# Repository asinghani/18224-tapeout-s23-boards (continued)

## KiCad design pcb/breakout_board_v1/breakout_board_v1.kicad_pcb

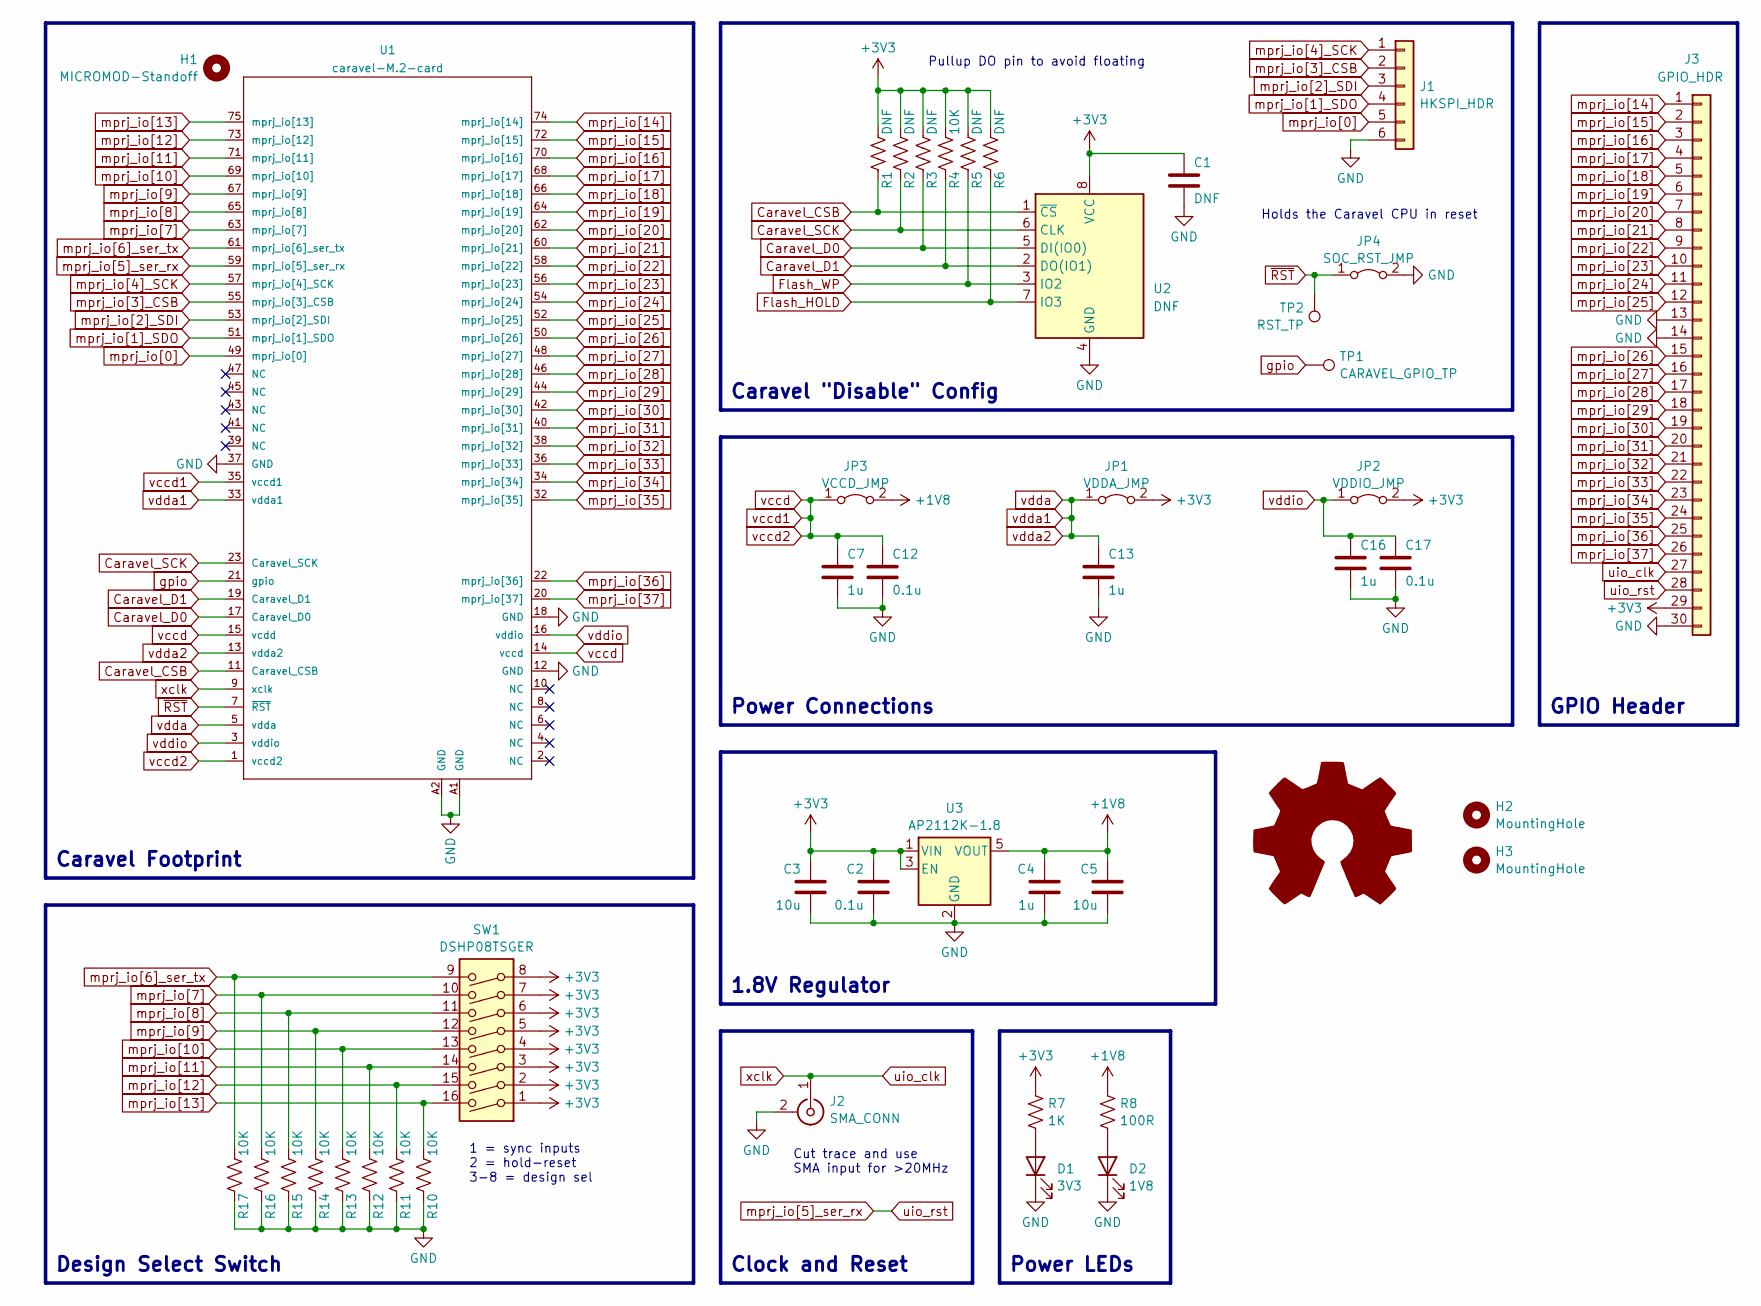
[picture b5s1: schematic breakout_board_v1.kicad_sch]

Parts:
C1: DNF; C_0603_1608Metric_Pad1.08x0.95mm_HandSolder
C2, C12, C17: 0.1u; C_0603_1608Metric; LCSC C14663
C3, C5: 10u; C_0603_1608Metric; LCSC C19702
C4, C7, C13, C16: 1u; C_0603_1608Metric; LCSC C15849
D1: 3V3; LED_0805_2012Metric; LCSC C98221
D2: 1V8; LED_0805_2012Metric; LCSC C98221
H1: MICROMOD-Standoff; MicroMod-Standoff
H2, H3: MountingHole; MountingHole_3.2mm_M3_Pad_Via
J1: HKSPI_HDR; PinHeader_1x06_P2.54mm_Vertical
J2: SMA_CONN; SMB_Jack_Vertical
J3: GPIO_HDR; PinHeader_1x30_P2.54mm_Vertical
JP1: VDDA_JMP; SolderJumper-2_P1.3mm_Bridged2Bar_Pad1.0x1.5mm
JP2: VDDIO_JMP; SolderJumper-2_P1.3mm_Bridged2Bar_Pad1.0x1.5mm
JP3: VCCD_JMP; SolderJumper-2_P1.3mm_Bridged2Bar_Pad1.0x1.5mm
JP4: SOC_RST_JMP; SolderJumper-2_P1.3mm_Bridged2Bar_Pad1.0x1.5mm
R1, R2, R3, R5, R6: DNF; R_0805_2012Metric
R4, R10, R11, R12, R13, R14, R15, R16, R17: 10K; R_0805_2012Metric; LCSC C17414
R7: 1K; R_0805_2012Metric; LCSC C17513
R8: 100R; R_0805_2012Metric; LCSC C17408
SW1: DSHP08TSGER; SW_DIP_SPSTx08_Slide_KingTek_DSHP08TS_W7.62mm_P1.27mm; LCSC C3293147
TP1: CARAVEL_GPIO_TP; TestPoint_Pad_D1.5mm
TP2: RST_TP; TestPoint_Pad_D1.5mm
U1: caravel-M.2-card; M.2-CONNECTOR-E; LCSC C2977809
U2: DNF; SOIC-8_5.23x5.23mm_P1.27mm
U3: AP2112K-1.8; SOT-23-5; LCSC C176944

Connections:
+1V8: C4.1, C5.1, JP3.2 (B), R8.2, U3.5 (VOUT)
+3V3: C1.1, C2.1, C3.1, J3.29, JP1.2 (B), JP2.2 (B), R1.1, R2.1, R3.1, R4.1, R5.1, R6.1, R7.2, SW1.1, SW1.2, SW1.3, SW1.4, SW1.5, SW1.6, SW1.7, SW1.8, U2.8 (VCC), U3.1 (VIN), U3.3 (EN)
Caravel_CSB: R1.2, U1.11 (Caravel_CSB), U2.1 (~CS)
Caravel_D0: R3.2, U1.17 (Caravel_D0), U2.5 (DI(IO0))
Caravel_D1: R4.2, U1.19 (Caravel_D1), U2.2 (DO(IO1))
Caravel_SCK: R2.2, U1.23 (Caravel_SCK), U2.6 (CLK)
Flash_HOLD: R6.2, U2.7 (IO3)
Flash_WP: R5.2, U2.3 (IO2)
GND: C1.2, C2.2, C3.2, C4.2, C5.2, C7.2, C12.2, C13.2, C16.2, C17.2, D1.1 (K), D2.1 (K), J1.6, J2.2 (Ext), J3.13, J3.14, J3.30, JP4.2 (B), R10.2, R11.2, R12.2, R13.2, R14.2, R15.2, R16.2, R17.2, U1.12 (GND), U1.18 (GND), U1.37 (GND), U1.A1 (GND), U1.A2 (GND), U2.4 (GND), U3.2 (GND)
unnamed: D1.2 (A), R7.1
unnamed: D2.2 (A), R8.1
gpio: TP1.1, U1.21 (gpio)
mprj_io[0]: J1.5, U1.49 (mprj_io[0])
mprj_io[1]_SDO: J1.4, U1.51 (mprj_io[1]_SDO)
mprj_io[2]_SDI: J1.3, U1.53 (mprj_io[2]_SDI)
mprj_io[3]_CSB: J1.2, U1.55 (mprj_io[3]_CSB)
mprj_io[4]_SCK: J1.1, U1.57 (mprj_io[4]_SCK)
mprj_io[5]_ser_rx: J3.28, U1.59 (mprj_io[5]_ser_rx)
mprj_io[6]_ser_tx: R17.1, SW1.9, U1.61 (mprj_io[6]_ser_tx)
mprj_io[7]: R16.1, SW1.10, U1.63 (mprj_io[7])
mprj_io[8]: R15.1, SW1.11, U1.65 (mprj_io[8])
mprj_io[9]: R14.1, SW1.12, U1.67 (mprj_io[9])
mprj_io[10]: R13.1, SW1.13, U1.69 (mprj_io[10])
mprj_io[11]: R12.1, SW1.14, U1.71 (mprj_io[11])
mprj_io[12]: R11.1, SW1.15, U1.73 (mprj_io[12])
mprj_io[13]: R10.1, SW1.16, U1.75 (mprj_io[13])
mprj_io[14]: J3.1, U1.74 (mprj_io[14])
mprj_io[15]: J3.2, U1.72 (mprj_io[15])
mprj_io[16]: J3.3, U1.70 (mprj_io[16])
mprj_io[17]: J3.4, U1.68 (mprj_io[17])
mprj_io[18]: J3.5, U1.66 (mprj_io[18])
mprj_io[19]: J3.6, U1.64 (mprj_io[19])
mprj_io[20]: J3.7, U1.62 (mprj_io[20])
mprj_io[21]: J3.8, U1.60 (mprj_io[21])
mprj_io[22]: J3.9, U1.58 (mprj_io[22])
mprj_io[23]: J3.10, U1.56 (mprj_io[23])
mprj_io[24]: J3.11, U1.54 (mprj_io[24])
mprj_io[25]: J3.12, U1.52 (mprj_io[25])
mprj_io[26]: J3.15, U1.50 (mprj_io[26])
mprj_io[27]: J3.16, U1.48 (mprj_io[27])
mprj_io[28]: J3.17, U1.46 (mprj_io[28])
mprj_io[29]: J3.18, U1.44 (mprj_io[29])
mprj_io[30]: J3.19, U1.42 (mprj_io[30])
mprj_io[31]: J3.20, U1.40 (mprj_io[31])
mprj_io[32]: J3.21, U1.38 (mprj_io[32])
mprj_io[33]: J3.22, U1.36 (mprj_io[33])
mprj_io[34]: J3.23, U1.34 (mprj_io[34])
mprj_io[35]: J3.24, U1.32 (mprj_io[35])
mprj_io[36]: J3.25, U1.22 (mprj_io[36])
mprj_io[37]: J3.26, U1.20 (mprj_io[37])
uio_clk: J2.1 (In), J3.27, U1.9 (xclk)
vccd: C7.1, C12.1, JP3.1 (A), U1.1 (vccd2), U1.14 (vccd), U1.15 (vcdd), U1.35 (vccd1)
vdda: C13.1, JP1.1 (A), U1.5 (vdda), U1.13 (vdda2), U1.33 (vdda1)
vddio: C16.1, C17.1, JP2.1 (A), U1.3 (vddio), U1.16 (vddio)
~RST: JP4.1 (A), TP2.1, U1.7 (~RST)

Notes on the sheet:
Power Connections
Caravel Footprint
Power LEDs
1.8V Regulator
Design Select Switch
Caravel "Disable" Config
Cut trace and use SMA input for >20MHz
Pullup DO pin to avoid floating
Clock and Reset
GPIO Header
1 = sync inputs 2 = hold-reset 3-8 = design sel
Holds the Caravel CPU in reset

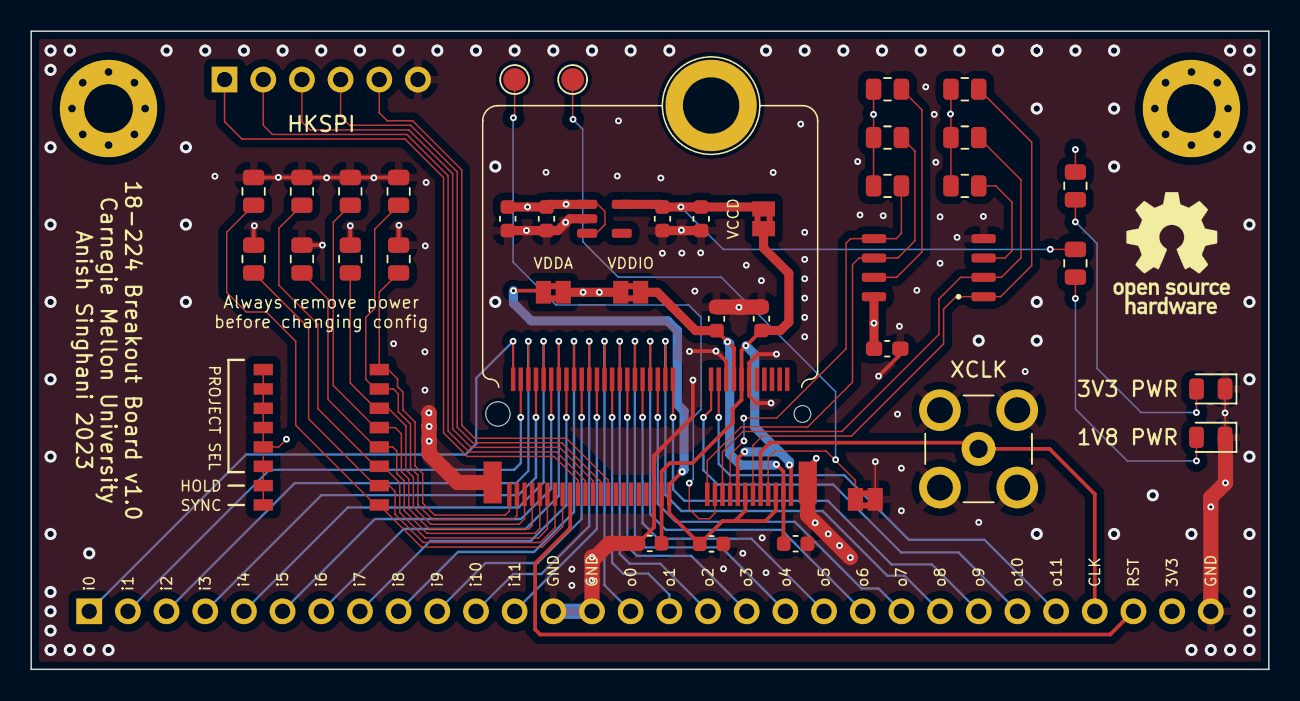
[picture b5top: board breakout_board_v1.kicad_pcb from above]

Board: 4 copper layers, 81.3 x 41.9 mm, 44 parts (0 on the bottom side), 55 nets.

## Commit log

2023-11-26 Import PCB
2023-11-26 add buffered version of board
2023-11-26 cleanup boards
2023-12-14 Import finished PCB designs
2023-12-14 Import HKSPI test scripts 2023-12-23
2023-12-22 Import debugger firmware
2023-12-22 Import debug interface Python
2023-12-22 updates to test interface, add d11 test
2023-12-22 add d18 test
2023-12-22 add d22 test
2024-04-07 Add latest PCB version + preliminary ASSEMBLY docs
2024-04-07 Fix TC connector
2024-04-07 Image width fix
2024-04-10 wip on docs
2024-05-03 updated docs
2024-05-03 cleanup
2024-05-04 fix comment
2024-05-07 Add ERRATA
2024-12-08 Add breakout board v4
